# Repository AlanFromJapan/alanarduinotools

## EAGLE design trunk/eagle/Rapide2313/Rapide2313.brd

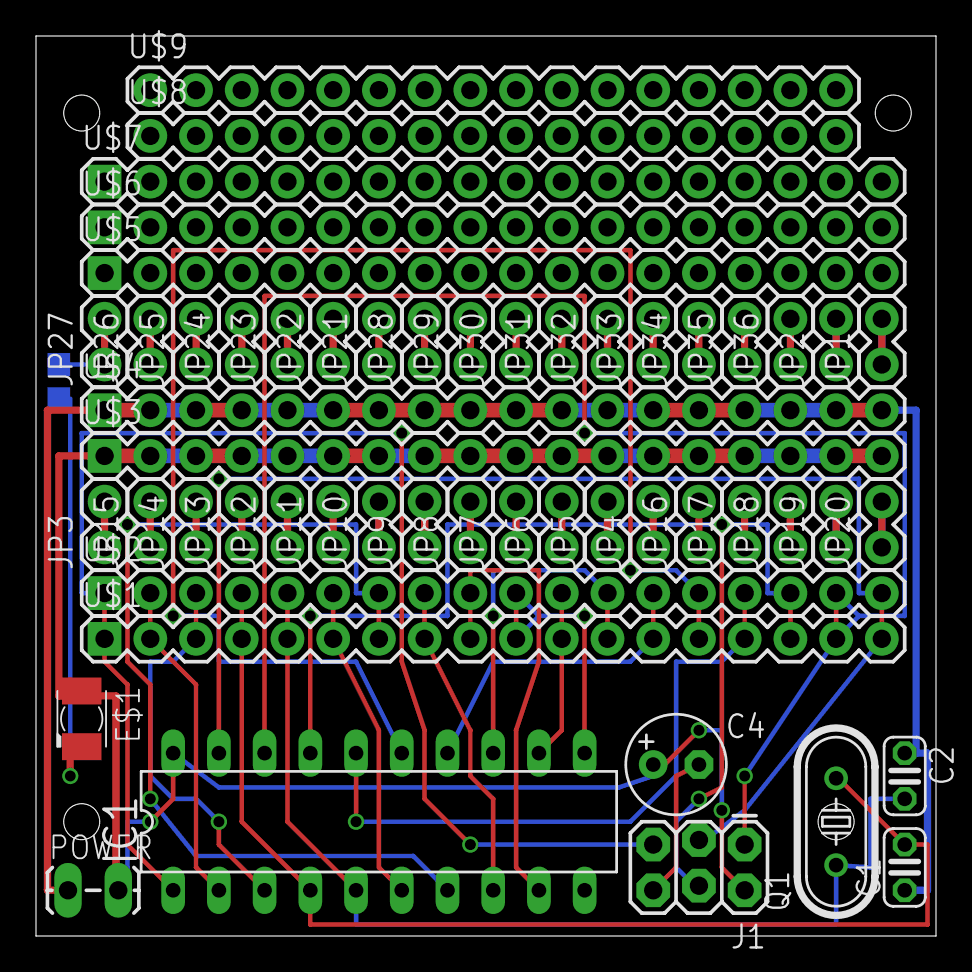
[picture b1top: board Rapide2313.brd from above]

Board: 2 copper layers, 50.0 x 50.0 mm, 53 parts (0 on the bottom side), 56 nets.

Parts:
C1, C2: 22pF; C025-024X044
C4: E2,5-6
E$1: KA-3528ASYC
IC1: AT90S2313P; DIL20
J1: AVR_SPI_PRG_62X3_LOCK; 2X3_LOCK
JP1, JP2, JP3, JP4, JP5, JP6, JP7, JP8, JP9, JP10, JP11, JP12, JP13, JP14, JP15, JP16, JP17, JP18, JP19, JP20, JP21, JP22, JP23, JP24, JP25, JP26, JP27, JP28, JP29, JP30, JP31, JP32, JP33, JP34, JP35, JP36: 1X02
POWER: 1X02_LOCK_LONGPADS
Q1: HC49/S
U$1, U$2, U$3, U$4, U$5, U$6, U$7: M18_; 1X18
U$8, U$9: M18_; 1X16

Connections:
GND: C1.1, C2.1, C4.-, IC1.10, J1.6, U$4.1, U$4.2, U$4.3, U$4.4, U$4.5, U$4.6, U$4.11, U$4.12, U$4.13, U$4.15, U$4.16, U$4.17, U$4.18
MISO: IC1.18, J1.1, U$1.17, U$2.17
MOSI: IC1.17, J1.4, U$1.16, U$2.16
unnamed: C1.2, IC1.4, Q1.2, U$1.4, U$2.4
unnamed: C2.2, IC1.5, Q1.1, U$1.5, U$2.5
unnamed: IC1.2, U$1.2, U$2.2
unnamed: IC1.3, U$1.3, U$2.3
unnamed: IC1.6, U$1.6, U$2.6
unnamed: IC1.7, U$1.7, U$2.7
unnamed: IC1.8, U$1.8, U$2.8
unnamed: IC1.9, U$1.9, U$2.9
unnamed: IC1.11, U$1.10, U$2.10
unnamed: IC1.12, U$1.11, U$2.11
unnamed: IC1.13, U$1.12, U$2.12
unnamed: IC1.14, U$1.13, U$2.13
unnamed: IC1.15, U$1.14, U$2.14
unnamed: IC1.16, U$1.15, U$2.15
RESET: IC1.1, J1.5, U$1.1, U$2.1
S$1: JP27.1, JP27.2
S$2: JP24.1, JP24.2
S$4: JP23.1, JP23.2
S$5: JP22.1, JP22.2
S$6: JP21.1, JP21.2
S$7: JP28.1, JP28.2
S$8: JP29.1, JP29.2
S$9: JP30.1, JP30.2
S$10: JP31.1, JP31.2
S$11: JP32.1, JP32.2
S$12: JP3.1, JP3.2
S$13: JP10.1, JP10.2
S$14: JP9.1, JP9.2
S$15: JP18.1, JP18.2
S$16: JP19.1, JP19.2
S$17: JP20.1, JP20.2
S$18: JP1.1, JP1.2
S$19: JP2.1, JP2.2
S$21: JP26.1, JP26.2
S$22: JP25.1, JP25.2
S$23: JP33.1, JP33.2
S$24: JP34.1, JP34.2
S$25: JP35.1, JP35.2
S$26: JP36.1, JP36.2
S$27: JP17.1, JP17.2
S$28: JP16.1, JP16.2
S$29: JP4.1, JP4.2
S$30: JP5.1, JP5.2
S$31: JP6.1, JP6.2
S$32: JP7.1, JP7.2
S$33: JP8.1, JP8.2
S$34: JP11.1, JP11.2
S$35: JP12.1, JP12.2
S$36: JP13.1, JP13.2
S$37: JP14.1, JP14.2
S$38: JP15.1, JP15.2
SCK: IC1.19, J1.3, U$1.18, U$2.18
VCC: C4.+, IC1.20, J1.2, POWER.2, U$3.1, U$3.2, U$3.3, U$3.4, U$3.5, U$3.6, U$3.7, U$3.8, U$3.12, U$3.13, U$3.15, U$3.16, U$3.17, U$3.18

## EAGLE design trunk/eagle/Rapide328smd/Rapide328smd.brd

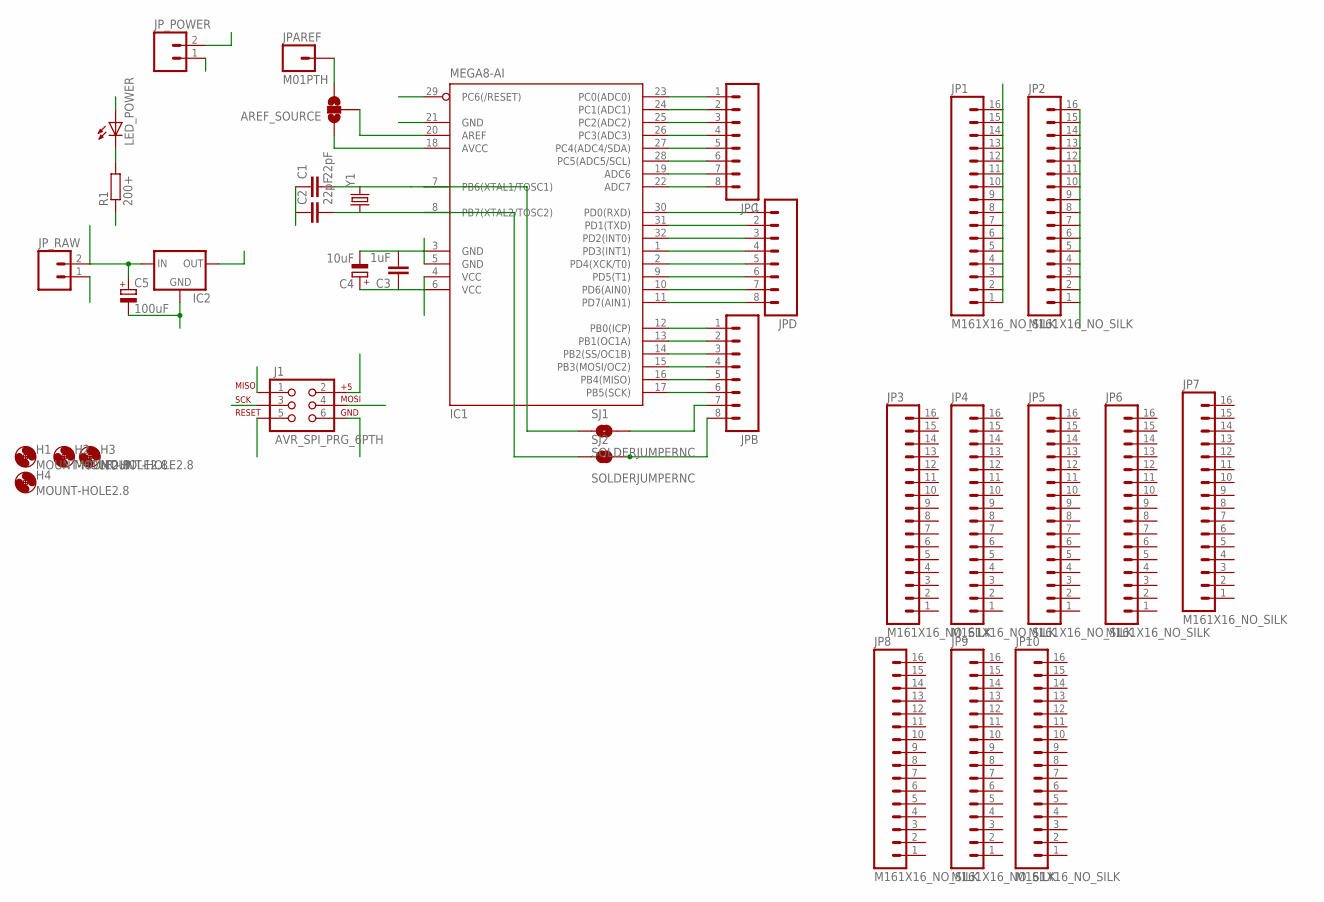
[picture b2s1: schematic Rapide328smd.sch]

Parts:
AREF_SOURCE: SOLDERJUMPER_2WAYPASTE1&2; SJ_3_PASTE1&2
C1, C2: 22pF; C025-024X044
C3: 1uF; C025-024X044
C4: 10uF; E2-5
C5: 100uF; E2-5
H1, H2, H3, H4: MOUNT-HOLE2.8; 2,8
IC1: MEGA8-AI; TQFP32-08
IC2: V_REG_78XXSINK; TO220-IGO
J1: AVR_SPI_PRG_6PTH; 2X3
JP1, JP2, JP3, JP4, JP5, JP6, JP7, JP8, JP9, JP10: M161X16_NO_SILK; 1X16_NO_SILK
JPAREF: M01PTH; 1X01
JPB: M081X08; 1X08
JPC: M081X08; 1X08
JPD: M081X08; 1X08
JP_POWER: M02PTH3; 1X02_LONGPADS
JP_RAW: M02PTH3; 1X02_LONGPADS
LED_POWER: LEDKA-3528ASYC; KA-3528ASYC
R1: 200+; 0204/7
SJ1, SJ2: SOLDERJUMPERNC; SJ_2S
Y1: CRYSTALHC49UV; HC49U-V

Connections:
GND: C1.1, C2.1, C3.2, C4.-, C5.-, IC1.3 (GND), IC1.5 (GND), IC1.21 (GND), IC2.GND, J1.6, JP2.1, JP2.2, JP2.3, JP2.4, JP2.5, JP2.6, JP2.7, JP2.8, JP2.9, JP2.10, JP2.11, JP2.12, JP2.13, JP2.14, JP2.15, JP2.16, JP_POWER.1, JP_RAW.1, R1.1
MISO: IC1.16 (PB4(MISO)), J1.1, JPB.5
MOSI: IC1.15 (PB3(MOSI/OC2)), J1.4, JPB.4
unnamed: C1.2, IC1.7 (PB6(XTAL1/TOSC1)), SJ1.1, Y1.2
unnamed: IC1.25 (PC2(ADC2)), JPC.3
unnamed: IC1.24 (PC1(ADC1)), JPC.2
unnamed: IC1.23 (PC0(ADC0)), JPC.1
unnamed: IC1.22 (ADC7), JPC.8
unnamed: IC1.19 (ADC6), JPC.7
unnamed: IC1.28 (PC5(ADC5/SCL)), JPC.6
unnamed: IC1.27 (PC4(ADC4/SDA)), JPC.5
unnamed: IC1.26 (PC3(ADC3)), JPC.4
unnamed: AREF_SOURCE.2, IC1.20 (AREF)
unnamed: IC1.12 (PB0(ICP)), JPB.1
unnamed: IC1.13 (PB1(OC1A)), JPB.2
unnamed: IC1.14 (PB2(SS/OC1B)), JPB.3
unnamed: JPB.7, SJ1.2
unnamed: JPB.8, SJ2.2
unnamed: C2.2, IC1.8 (PB7(XTAL2/TOSC2)), SJ2.1, Y1.1
unnamed: AREF_SOURCE.3, JPAREF.1
unnamed: IC1.11 (PD7(AIN1)), JPD.8
unnamed: LED_POWER.C, R1.2
unnamed: IC1.10 (PD6(AIN0)), JPD.7
unnamed: IC1.9 (PD5(T1)), JPD.6
unnamed: IC1.2 (PD4(XCK/T0)), JPD.5
unnamed: IC1.1 (PD3(INT1)), JPD.4
unnamed: IC1.32 (PD2(INT0)), JPD.3
unnamed: IC1.31 (PD1(TXD)), JPD.2
unnamed: IC1.30 (PD0(RXD)), JPD.1
RESET: IC1.29 (PC6(/RESET)), J1.5
SCK: IC1.17 (PB5(SCK)), J1.3, JPB.6
VCC: AREF_SOURCE.1, C3.1, C4.+, IC1.4 (VCC), IC1.6 (VCC), IC1.18 (AVCC), IC2.OUT, J1.2, JP1.1, JP1.2, JP1.3, JP1.4, JP1.5, JP1.6, JP1.7, JP1.8, JP1.9, JP1.10, JP1.11, JP1.12, JP1.13, JP1.14, JP1.15, JP1.16, JP_POWER.2, LED_POWER.A
VRAW: C5.+, IC2.IN, JP_RAW.2

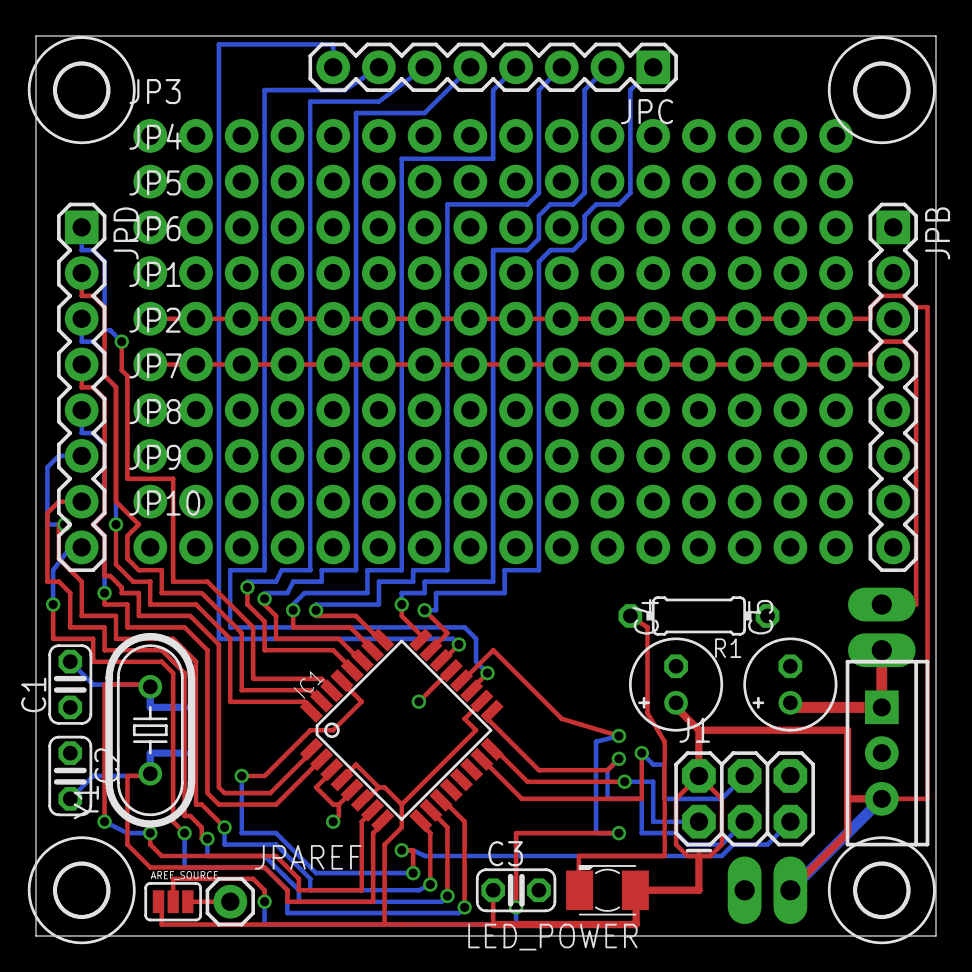
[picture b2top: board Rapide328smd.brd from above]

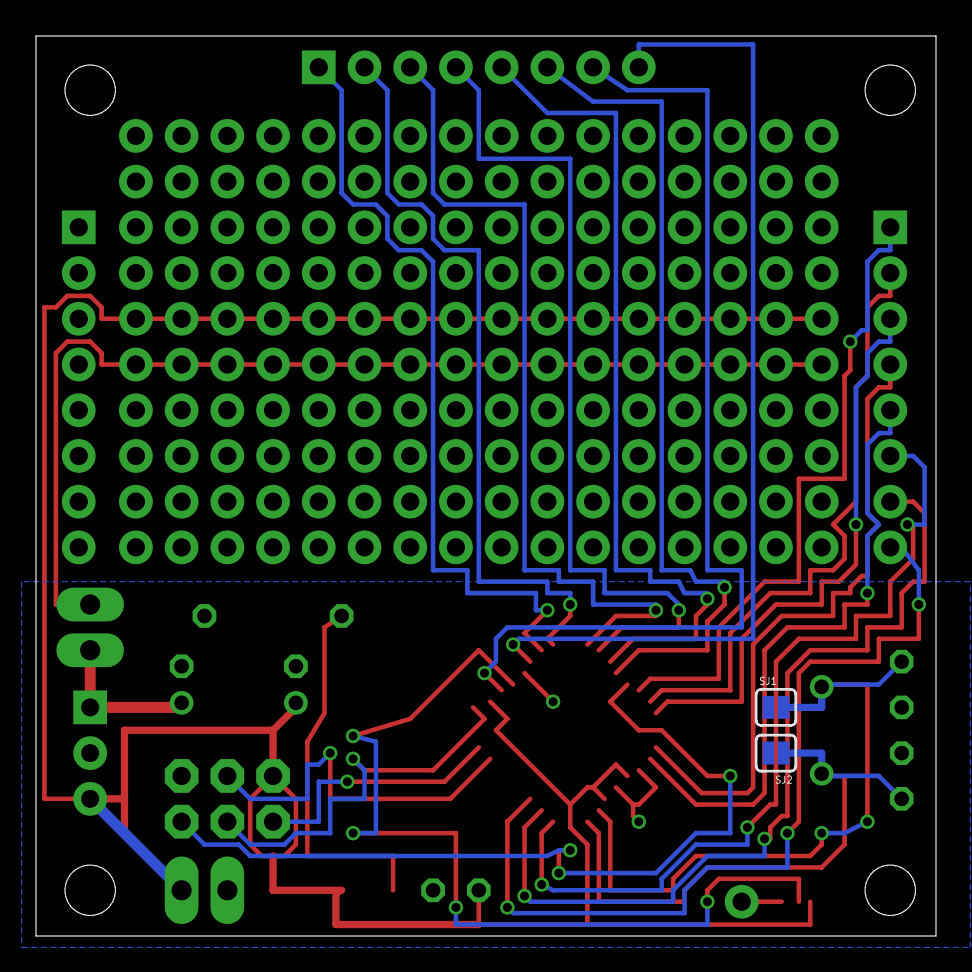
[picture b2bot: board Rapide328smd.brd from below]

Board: 2 copper layers, 50.0 x 50.0 mm, 34 parts (2 on the bottom side), 33 nets.

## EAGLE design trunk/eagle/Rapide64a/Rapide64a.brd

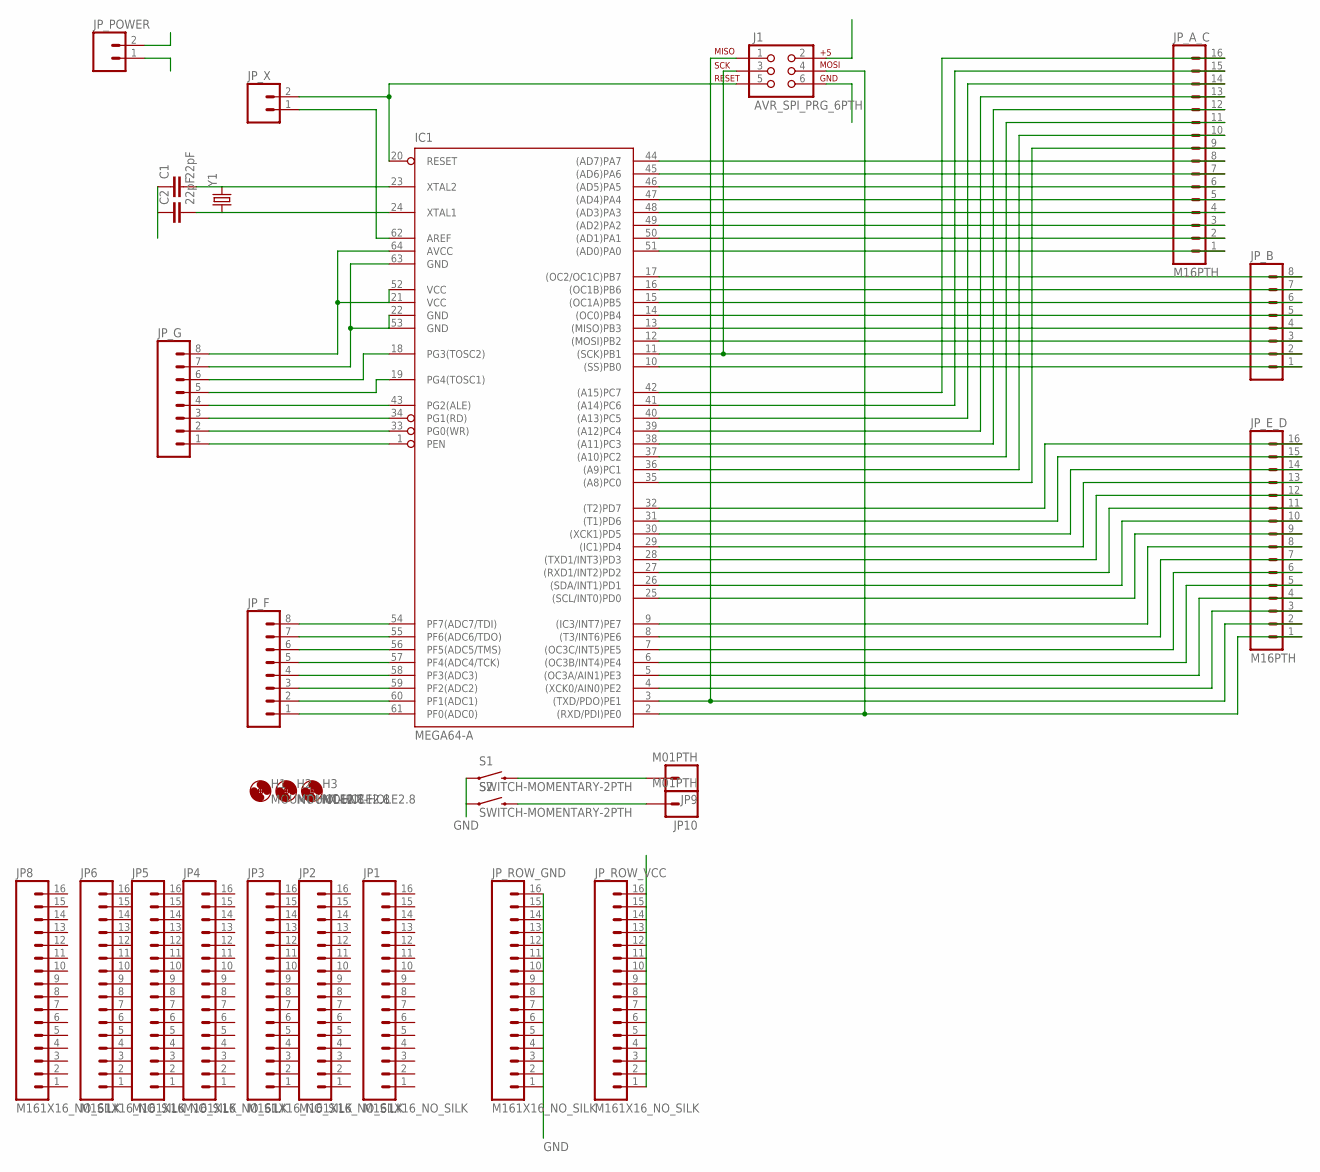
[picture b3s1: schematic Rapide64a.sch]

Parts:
C1, C2: 22pF; C025-024X044
H1, H2, H3: MOUNT-HOLE2.8; 2,8
IC1: MEGA64-A; TQFP64
J1: AVR_SPI_PRG_6PTH; 2X3
JP1, JP2, JP3, JP4, JP5, JP6, JP8: M161X16_NO_SILK; 1X16_NO_SILK
JP9, JP10: M01PTH; 1X01
JP_A_C: M16PTH; 1X16
JP_B: M081X08; 1X08
JP_E_D: M16PTH; 1X16
JP_F: M081X08; 1X08
JP_G: M081X08; 1X08
JP_POWER: M02PTH; 1X02
JP_ROW_GND: M161X16_NO_SILK; 1X16_NO_SILK
JP_ROW_VCC: M161X16_NO_SILK; 1X16_NO_SILK
JP_X: M02PTH; 1X02
S1, S2: SWITCH-MOMENTARY-2PTH; TACTILE-PTH
Y1: CRYSTALHC49UV; HC49U-V

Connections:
GND: C1.1, C2.1, IC1.22 (GND), IC1.53 (GND), IC1.63 (GND), J1.6, JP_G.7, JP_POWER.1, JP_ROW_GND.1, JP_ROW_GND.2, JP_ROW_GND.3, JP_ROW_GND.4, JP_ROW_GND.5, JP_ROW_GND.6, JP_ROW_GND.7, JP_ROW_GND.8, JP_ROW_GND.9, JP_ROW_GND.10, JP_ROW_GND.11, JP_ROW_GND.12, JP_ROW_GND.13, JP_ROW_GND.14, JP_ROW_GND.15, JP_ROW_GND.16, S1.1, S2.1
MISO: IC1.3 ((TXD/PDO)PE1), J1.1, JP_E_D.2
MOSI: IC1.2 ((RXD/PDI)PE0), J1.4, JP_E_D.1
unnamed: IC1.6 ((OC3B/INT4)PE4), JP_E_D.5
unnamed: IC1.7 ((OC3C/INT5)PE5), JP_E_D.6
unnamed: IC1.8 ((T3/INT6)PE6), JP_E_D.7
unnamed: IC1.25 ((SCL/INT0)PD0), JP_E_D.9
unnamed: IC1.9 ((IC3/INT7)PE7), JP_E_D.8
unnamed: IC1.26 ((SDA/INT1)PD1), JP_E_D.10
unnamed: IC1.27 ((RXD1/INT2)PD2), JP_E_D.11
unnamed: IC1.58 (PF3(ADC3)), JP_F.4
unnamed: IC1.57 (PF4(ADC4/TCK)), JP_F.5
unnamed: IC1.56 (PF5(ADC5/TMS)), JP_F.6
unnamed: IC1.55 (PF6(ADC6/TDO)), JP_F.7
unnamed: IC1.54 (PF7(ADC7/TDI)), JP_F.8
unnamed: IC1.48 ((AD3)PA3), JP_A_C.4
unnamed: IC1.10 ((SS)PB0), JP_B.1
unnamed: IC1.49 ((AD2)PA2), JP_A_C.3
unnamed: IC1.17 ((OC2/OC1C)PB7), JP_B.8
unnamed: IC1.1 (PEN), JP_G.1
unnamed: IC1.33 (PG0(WR)), JP_G.2
unnamed: IC1.34 (PG1(RD)), JP_G.3
unnamed: IC1.18 (PG3(TOSC2)), JP_G.6
unnamed: IC1.19 (PG4(TOSC1)), JP_G.5
unnamed: IC1.39 ((A12)PC4), JP_A_C.13
unnamed: IC1.12 ((MOSI)PB2), JP_B.3
unnamed: IC1.13 ((MISO)PB3), JP_B.4
unnamed: IC1.43 (PG2(ALE)), JP_G.4
unnamed: IC1.47 ((AD4)PA4), JP_A_C.5
unnamed: IC1.46 ((AD5)PA5), JP_A_C.6
unnamed: IC1.45 ((AD6)PA6), JP_A_C.7
unnamed: JP9.1, S1.3 (2)
unnamed: IC1.14 ((OC0)PB4), JP_B.5
unnamed: IC1.51 ((AD0)PA0), JP_A_C.1
unnamed: IC1.50 ((AD1)PA1), JP_A_C.2
unnamed: IC1.15 ((OC1A)PB5), JP_B.6
unnamed: JP10.1, S2.3 (2)
unnamed: IC1.44 ((AD7)PA7), JP_A_C.8
unnamed: IC1.16 ((OC1B)PB6), JP_B.7
unnamed: IC1.42 ((A15)PC7), JP_A_C.16
unnamed: IC1.41 ((A14)PC6), JP_A_C.15
unnamed: IC1.40 ((A13)PC5), JP_A_C.14
unnamed: IC1.35 ((A8)PC0), JP_A_C.9
unnamed: IC1.62 (AREF), JP_X.1
unnamed: C1.2, IC1.23 (XTAL2), Y1.2
unnamed: C2.2, IC1.24 (XTAL1), Y1.1
unnamed: IC1.4 ((XCK0/AIN0)PE2), JP_E_D.3
unnamed: IC1.5 ((OC3A/AIN1)PE3), JP_E_D.4
unnamed: IC1.28 ((TXD1/INT3)PD3), JP_E_D.12
unnamed: IC1.29 ((IC1)PD4), JP_E_D.13
unnamed: IC1.30 ((XCK1)PD5), JP_E_D.14
unnamed: IC1.31 ((T1)PD6), JP_E_D.15
unnamed: IC1.32 ((T2)PD7), JP_E_D.16
unnamed: IC1.38 ((A11)PC3), JP_A_C.12
unnamed: IC1.61 (PF0(ADC0)), JP_F.1
unnamed: IC1.60 (PF1(ADC1)), JP_F.2
unnamed: IC1.59 (PF2(ADC2)), JP_F.3
unnamed: IC1.37 ((A10)PC2), JP_A_C.11
unnamed: IC1.36 ((A9)PC1), JP_A_C.10
RESET: IC1.20 (RESET), J1.5, JP_X.2
SCK: IC1.11 ((SCK)PB1), J1.3, JP_B.2
VCC: IC1.21 (VCC), IC1.52 (VCC), IC1.64 (AVCC), J1.2, JP_G.8, JP_POWER.2, JP_ROW_VCC.1, JP_ROW_VCC.2, JP_ROW_VCC.3, JP_ROW_VCC.4, JP_ROW_VCC.5, JP_ROW_VCC.6, JP_ROW_VCC.7, JP_ROW_VCC.8, JP_ROW_VCC.9, JP_ROW_VCC.10, JP_ROW_VCC.11, JP_ROW_VCC.12, JP_ROW_VCC.13, JP_ROW_VCC.14, JP_ROW_VCC.15, JP_ROW_VCC.16

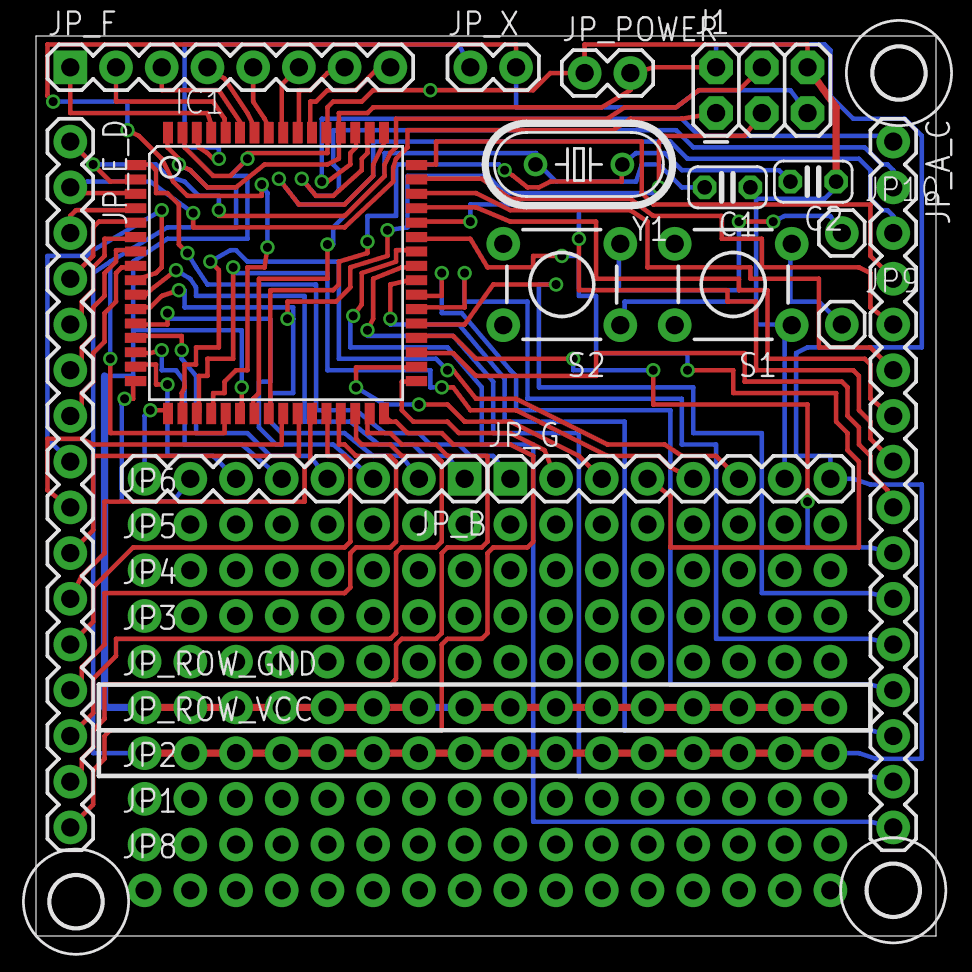
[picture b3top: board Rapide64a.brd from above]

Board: 2 copper layers, 50.0 x 50.0 mm, 28 parts (0 on the bottom side), 62 nets.

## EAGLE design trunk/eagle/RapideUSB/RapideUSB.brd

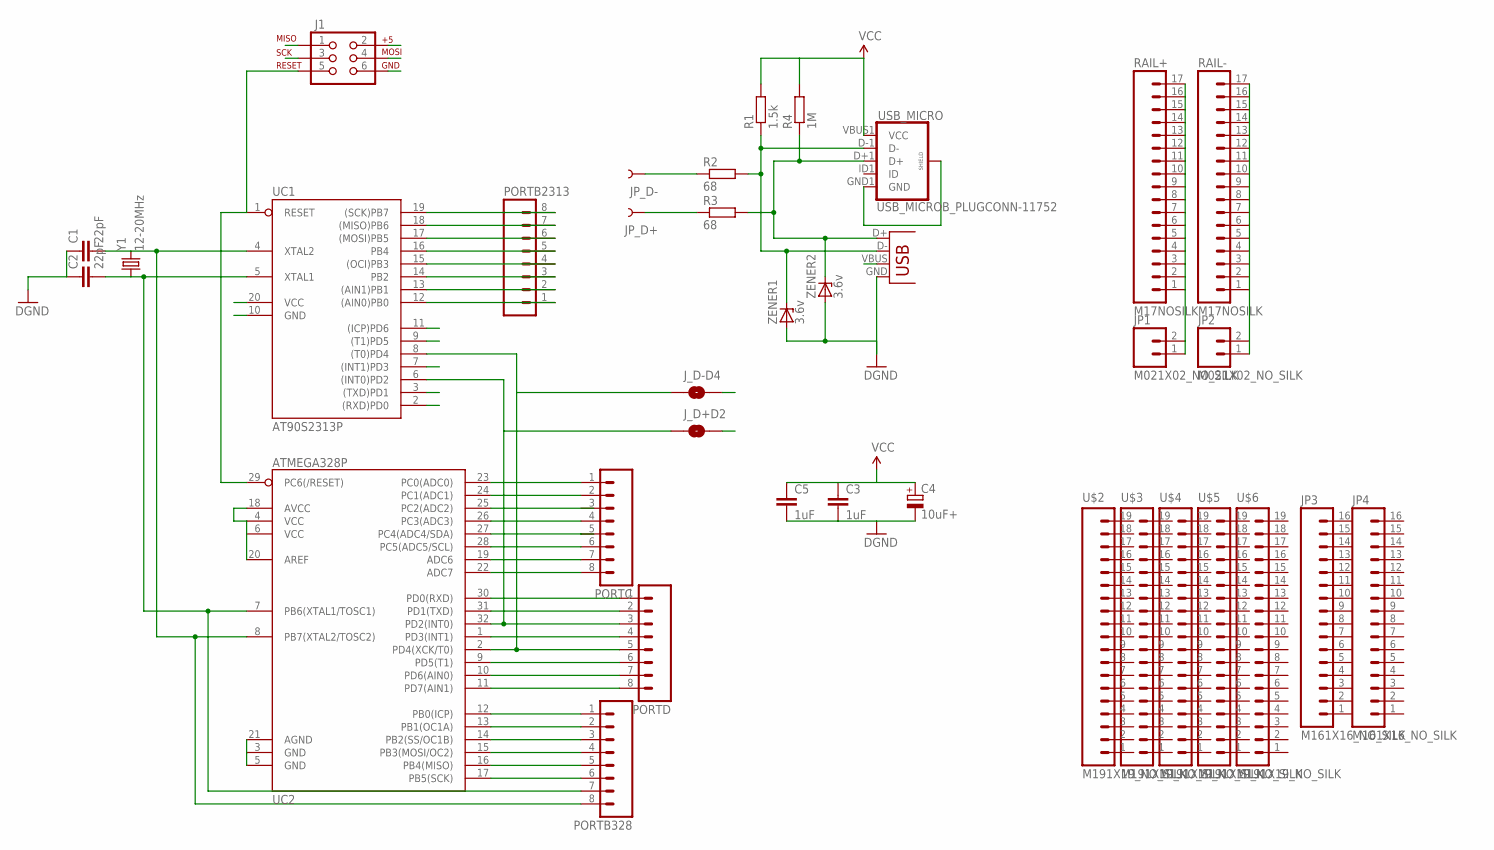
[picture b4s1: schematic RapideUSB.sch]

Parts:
C1, C2: 22pF; C025-024X044
C3, C5: 1uF; C025-024X044
C4: 10uF+; E2-5
J1: AVR_SPI_PRG_6PTH; 2X3
JP1, JP2: M021X02_NO_SILK; 1X02_NO_SILK
JP3, JP4: M161X16_NO_SILK; 1X16_NO_SILK
JP_D+: TEST-POINT3X5; PAD.03X.05
JP_D-: TEST-POINT3X5; PAD.03X.05
J_D+D2: JUMPER-PAD-2-NOYES_SILK; PAD-JUMPER-2-NO_YES_SILK
J_D-D4: JUMPER-PAD-2-NOYES_SILK; PAD-JUMPER-2-NO_YES_SILK
PORTB328, PORTB2313: M081X08; 1X08
PORTC: M081X08; 1X08
PORTD: M081X08; 1X08
R1: 1.5k; 0204V
R2, R3: 68; 0204V
R4: 1M; 0204V
RAIL+: M17NOSILK; 1X17_NO_SILK
RAIL-: M17NOSILK; 1X17_NO_SILK
U$2, U$3, U$4, U$5, U$6: M191X19_NO_SILK; 1X19_NO_SILK
UC1: AT90S2313P; DIL20
UC2: ATMEGA328P; TQFP32-08
USB_MICRO: USB_MICROB_PLUGCONN-11752; USB-B-MICRO-SMD_V03
USB_MINI: USBSMD; USB-MINIB
Y1: 12-20MHz; HC49U-V
ZENER1, ZENER2: 3.6v; ZDIO-2.5

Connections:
B0: PORTB328.1, UC2.12 (PB0(ICP))
B1: PORTB328.2, UC2.13 (PB1(OC1A))
B2: PORTB328.3, UC2.14 (PB2(SS/OC1B))
B6: C2.2, PORTB328.7, UC1.5 (XTAL1), UC2.7 (PB6(XTAL1/TOSC1)), Y1.1
B7: C1.2, PORTB328.8, UC1.4 (XTAL2), UC2.8 (PB7(XTAL2/TOSC2)), Y1.2
D0: PORTD.1, UC1.2 ((RXD)PD0), UC2.30 (PD0(RXD))
D1: PORTD.2, UC1.3 ((TXD)PD1), UC2.31 (PD1(TXD))
D2: J_D+D2.1, PORTD.3, UC1.6 ((INT0)PD2), UC2.32 (PD2(INT0))
D3: PORTD.4, UC1.7 ((INT1)PD3), UC2.1 (PD3(INT1))
D4: J_D-D4.1, PORTD.5, UC1.8 ((T0)PD4), UC2.2 (PD4(XCK/T0))
D5: UC1.9 ((T1)PD5)
D6: PORTD.7, UC1.11 ((ICP)PD6), UC2.10 (PD6(AIN0))
D7: PORTD.8, UC2.11 (PD7(AIN1))
D+: JP_D+.P$1, J_D+D2.2, R3.1
D-: JP_D-.P$1, J_D-D4.2, R2.1
GND: C1.1, C2.1, C3.2, C4.-, C5.2, J1.6, JP2.1, JP2.2, RAIL-.1, RAIL-.2, RAIL-.3, RAIL-.4, RAIL-.5, RAIL-.6, RAIL-.7, RAIL-.8, RAIL-.9, RAIL-.10, RAIL-.11, RAIL-.12, RAIL-.13, RAIL-.14, RAIL-.15, RAIL-.16, RAIL-.17, UC1.10 (GND), UC2.3 (GND), UC2.5 (GND), UC2.21 (AGND), USB_MICRO.GND1 (GND), USB_MICRO.SHIELD1 (SHIELD), USB_MICRO.SHIELD2 (SHIELD), USB_MICRO.SHIELD3 (SHIELD), USB_MINI.GND, ZENER1.A, ZENER2.A
MISO: J1.1, PORTB328.5, PORTB2313.7, UC1.18 ((MISO)PB6), UC2.16 (PB4(MISO))
MOSI: J1.4, PORTB328.4, PORTB2313.6, UC1.17 ((MOSI)PB5), UC2.15 (PB3(MOSI/OC2))
unnamed: PORTB2313.5, UC1.16 (PB4)
unnamed: PORTB2313.4, UC1.15 ((OCI)PB3)
unnamed: PORTB2313.3, UC1.14 (PB2)
unnamed: PORTB2313.2, UC1.13 ((AIN1)PB1)
unnamed: PORTC.1, UC2.23 (PC0(ADC0))
unnamed: PORTC.2, UC2.24 (PC1(ADC1))
unnamed: PORTC.4, UC2.26 (PC3(ADC3))
unnamed: PORTC.5, UC2.27 (PC4(ADC4/SDA))
unnamed: PORTC.6, UC2.28 (PC5(ADC5/SCL))
unnamed: PORTC.7, UC2.19 (ADC6)
unnamed: PORTC.8, UC2.22 (ADC7)
unnamed: PORTB2313.1, UC1.12 ((AIN0)PB0)
unnamed: PORTD.6, UC2.9 (PD5(T1))
RESET: J1.5, UC1.1 (RESET), UC2.29 (PC6(/RESET))
SCK: J1.3, PORTB328.6, PORTB2313.8, UC1.19 ((SCK)PB7), UC2.17 (PB5(SCK))
USBD+: R3.2, R4.1, USB_MICRO.D+1 (D+), USB_MINI.D+, ZENER2.C
USBD-: R1.1, R2.2, USB_MICRO.D-1 (D-), USB_MINI.D-, ZENER1.C
VCC: C3.1, C4.+, C5.1, J1.2, JP1.1, JP1.2, R1.2, R4.2, RAIL+.1, RAIL+.2, RAIL+.3, RAIL+.4, RAIL+.5, RAIL+.6, RAIL+.7, RAIL+.8, RAIL+.9, RAIL+.10, RAIL+.11, RAIL+.12, RAIL+.13, RAIL+.14, RAIL+.15, RAIL+.16, RAIL+.17, UC1.20 (VCC), UC2.4 (VCC), UC2.6 (VCC), UC2.18 (AVCC), UC2.20 (AREF), USB_MICRO.VBUS1 (VCC), USB_MINI.VBUS

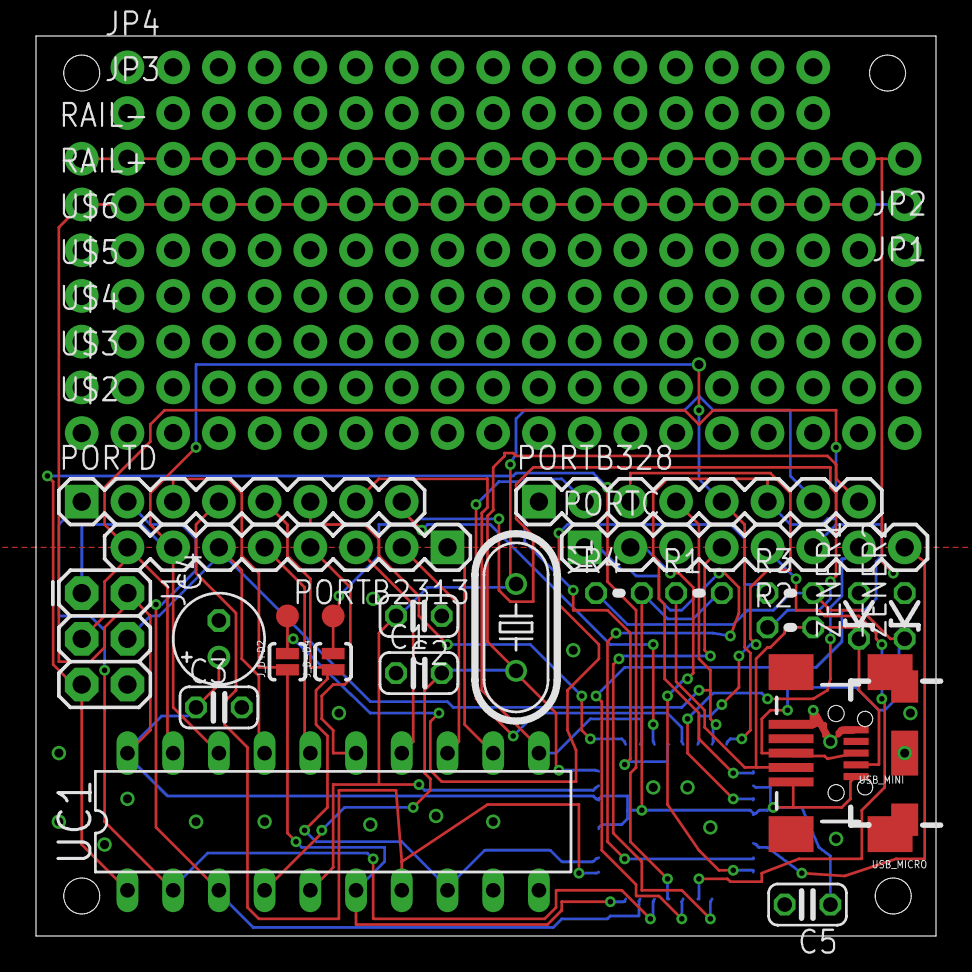
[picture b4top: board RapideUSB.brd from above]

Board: 4 copper layers, 50.0 x 50.0 mm, 37 parts (1 on the bottom side), 35 nets.

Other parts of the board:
U$1: VUSB_LOGO

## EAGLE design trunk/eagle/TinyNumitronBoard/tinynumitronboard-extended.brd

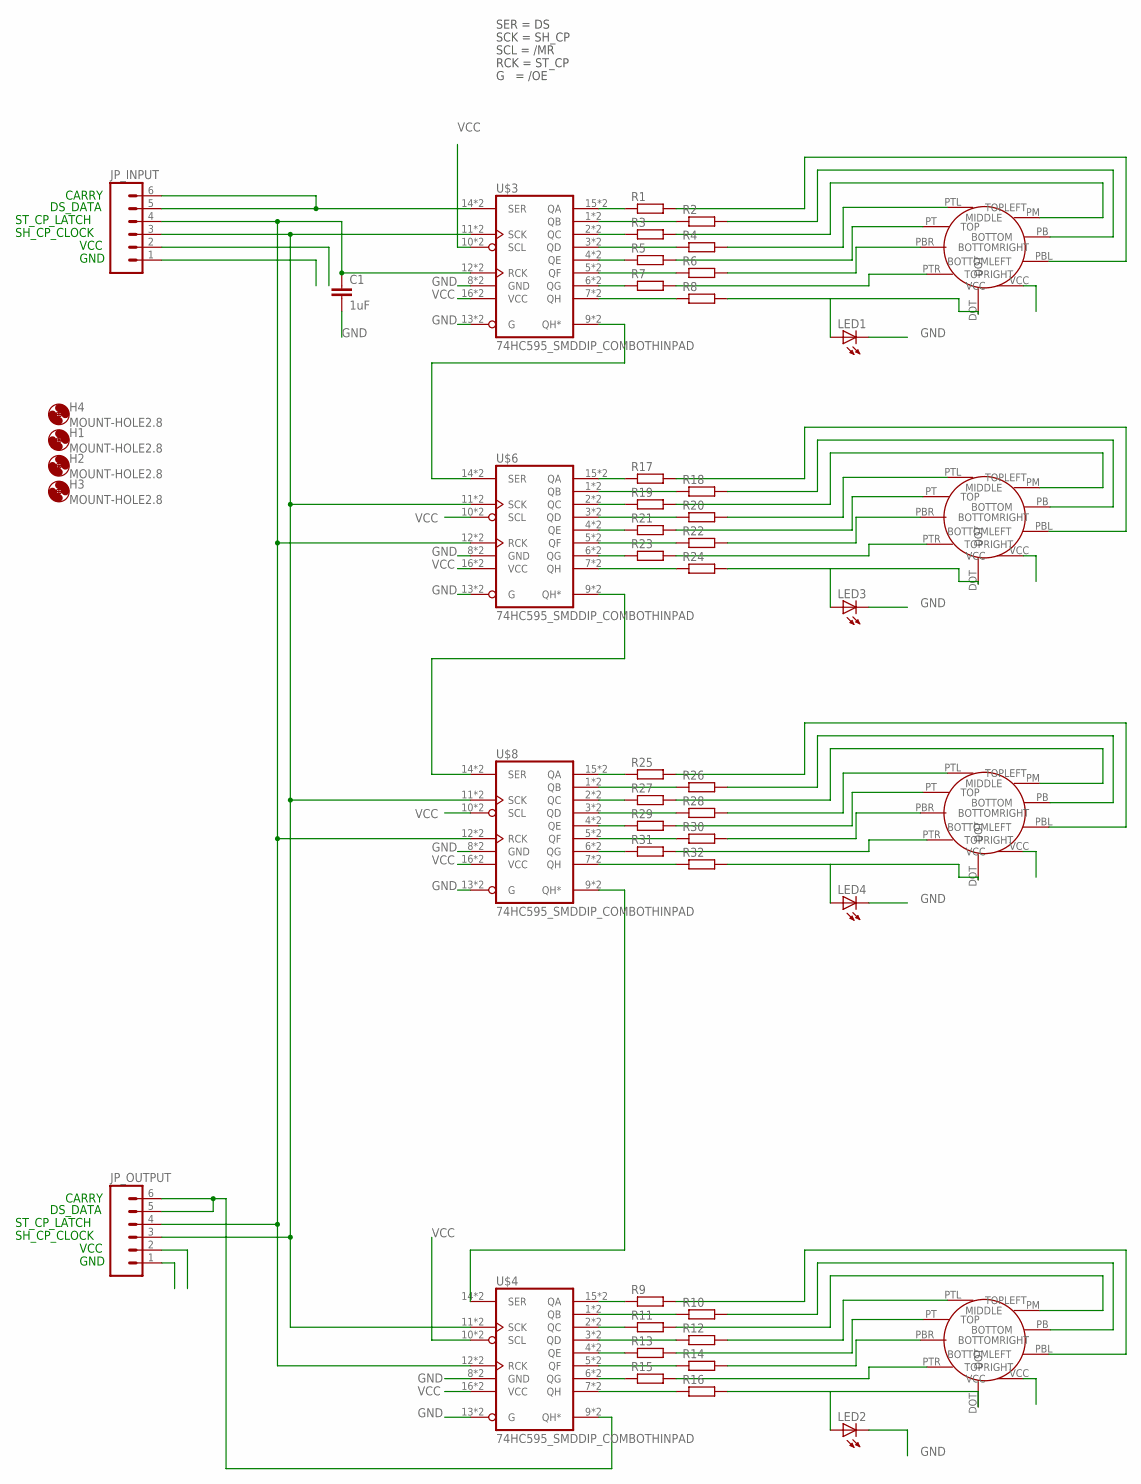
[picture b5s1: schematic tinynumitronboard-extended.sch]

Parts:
C1: 1uF; C050-024X044
H1, H2, H3, H4: MOUNT-HOLE2.8; 2,8
JP_INPUT: M06SIP; 1X06
JP_OUTPUT: M06SIP; 1X06
LED1, LED2, LED3, LED4: LEDKA-3528ASYC; KA-3528ASYC
R1, R2, R3, R4, R5, R6, R7, R8, R9, R10, R11, R12, R13, R14, R15, R16, R17, R18, R19, R20, R21, R22, R23, R24, R25, R26, R27, R28, R29, R30, R31, R32: R-EU_0207/10; 0207/10
U$1, U$2, U$5, U$7: IV16TINY_NUMITRON; IV16TINY_NUMITRON_PAC
U$3, U$4, U$6, U$8: 74HC595_SMDDIP_COMBOTHINPAD; DIL16_SO16_PAC2

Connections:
GND: C1.2, JP_INPUT.1, JP_OUTPUT.1, LED1.C, LED2.C, LED3.C, LED4.C, U$4.8 (GND), U$4.13 (G); also elsewhere on the board
unnamed: R1.2, U$1.PBL (BOTTOMLEFT)
unnamed: R2.2, U$1.PB (BOTTOM)
unnamed: R3.2, U$1.PM (MIDDLE)
unnamed: R4.2, U$1.PTL (TOPLEFT)
unnamed: R5.2, U$1.PT (TOP)
unnamed: R6.2, U$1.PBR (BOTTOMRIGHT)
unnamed: R7.2, U$1.PTR (TOPRIGHT)
unnamed 8: R1.1, U$3.15 (QA); also elsewhere on the board
unnamed 9: R2.1, U$3.1 (QB); also elsewhere on the board
unnamed 10: R3.1, U$3.2 (QC); also elsewhere on the board
unnamed 11: R4.1, U$3.3 (QD); also elsewhere on the board
unnamed 12: R5.1, U$3.4 (QE); also elsewhere on the board
unnamed 13: R6.1, U$3.5 (QF); also elsewhere on the board
unnamed 14: R7.1, U$3.6 (QG); also elsewhere on the board
unnamed 15: R8.1, U$3.7 (QH); also elsewhere on the board
unnamed: LED1.A, R8.2, U$1.DOT
unnamed: R9.2, U$2.PBL (BOTTOMLEFT)
unnamed: R10.2, U$2.PB (BOTTOM)
unnamed 19: JP_OUTPUT.5, JP_OUTPUT.6, U$4.9 (QH*); also elsewhere on the board
unnamed: R11.2, U$2.PM (MIDDLE)
unnamed: R12.2, U$2.PTL (TOPLEFT)
unnamed: R13.2, U$2.PT (TOP)
unnamed: R14.2, U$2.PBR (BOTTOMRIGHT)
unnamed: R15.2, U$2.PTR (TOPRIGHT)
unnamed 26: R9.1, U$4.15 (QA); also elsewhere on the board
unnamed 27: R10.1, U$4.1 (QB); also elsewhere on the board
unnamed 28: R11.1, U$4.2 (QC); also elsewhere on the board
unnamed 29: R12.1, U$4.3 (QD); also elsewhere on the board
unnamed 30: R13.1, U$4.4 (QE); also elsewhere on the board
unnamed 31: R14.1, U$4.5 (QF); also elsewhere on the board
unnamed 32: R15.1, U$4.6 (QG); also elsewhere on the board
unnamed 33: R16.1, U$4.7 (QH); also elsewhere on the board
unnamed: R17.2, U$5.PBL (BOTTOMLEFT)
unnamed: R18.2, U$5.PB (BOTTOM)
unnamed: R19.2, U$5.PM (MIDDLE)
unnamed: R20.2, U$5.PTL (TOPLEFT)
unnamed: R21.2, U$5.PT (TOP)
unnamed: R22.2, U$5.PBR (BOTTOMRIGHT)
unnamed: R23.2, U$5.PTR (TOPRIGHT)
unnamed 41: R17.1, U$6.15 (QA); also elsewhere on the board
unnamed 42: R18.1, U$6.1 (QB); also elsewhere on the board
unnamed 43: R19.1, U$6.2 (QC); also elsewhere on the board
unnamed 44: R20.1, U$6.3 (QD); also elsewhere on the board
unnamed 45: R21.1, U$6.4 (QE); also elsewhere on the board
unnamed 46: R22.1, U$6.5 (QF); also elsewhere on the board
unnamed 47: R23.1, U$6.6 (QG); also elsewhere on the board
unnamed 48: R24.1, U$6.7 (QH); also elsewhere on the board
unnamed: R25.2, U$7.PBL (BOTTOMLEFT)
unnamed: R26.2, U$7.PB (BOTTOM)
unnamed: R27.2, U$7.PM (MIDDLE)
unnamed: R28.2, U$7.PTL (TOPLEFT)
unnamed: R29.2, U$7.PT (TOP)
unnamed: R30.2, U$7.PBR (BOTTOMRIGHT)
unnamed: R31.2, U$7.PTR (TOPRIGHT)
unnamed 57: R25.1, U$8.15 (QA); also elsewhere on the board
unnamed 58: R26.1, U$8.1 (QB); also elsewhere on the board
unnamed 59: R27.1, U$8.2 (QC); also elsewhere on the board
unnamed 60: R28.1, U$8.3 (QD); also elsewhere on the board
unnamed 61: R29.1, U$8.4 (QE); also elsewhere on the board
unnamed 62: R30.1, U$8.5 (QF); also elsewhere on the board
unnamed 63: R31.1, U$8.6 (QG); also elsewhere on the board
unnamed 64: R32.1, U$8.7 (QH); also elsewhere on the board
RCK: C1.1, JP_INPUT.4, JP_OUTPUT.4, U$4.12 (RCK); also elsewhere on the board
SCK: JP_INPUT.3, JP_OUTPUT.3, U$4.11 (SCK); also elsewhere on the board
SER: JP_INPUT.5, JP_INPUT.6; also elsewhere on the board
VCC: JP_INPUT.2, JP_OUTPUT.2, U$1.VCC, U$2.VCC, U$4.10 (SCL), U$4.16 (VCC), U$5.VCC, U$7.VCC; also elsewhere on the board

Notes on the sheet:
SER = DS
SCK = SH_CP
SCL = /MR
RCK = ST_CP
G = /OE
GND
VCC
SH_CP_CLOCK
ST_CP_LATCH
DS_DATA
CARRY

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
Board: 2 copper layers, 51 parts (4 on the bottom side), 73 nets, no tracks yet.

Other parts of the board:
UC1, UC2, UC3, UC4: 74HC595_SMDDIP_COMBOTHINPAD; DIL16_SO16_PAC2

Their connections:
GND: UC1.8, UC1.13, UC1.S8, UC1.S13, UC2.8, UC2.13, UC2.S8, UC2.S13, UC3.8, UC3.13, UC3.S8, UC3.S13, UC4.8, UC4.13, UC4.S8, UC4.S13; also elsewhere on the board
unnamed 8: UC1.15, UC1.S15; also elsewhere on the board
unnamed 9: UC1.1, UC1.S1; also elsewhere on the board
unnamed 10: UC1.2, UC1.S2; also elsewhere on the board
unnamed 11: UC1.3, UC1.S3; also elsewhere on the board
unnamed 12: UC1.4, UC1.S4; also elsewhere on the board
unnamed 13: UC1.5, UC1.S5; also elsewhere on the board
unnamed 14: UC1.6, UC1.S6; also elsewhere on the board
unnamed 15: UC1.7, UC1.S7; also elsewhere on the board
unnamed 19: UC4.9, UC4.S9; also elsewhere on the board
unnamed: UC1.9, UC1.S9, UC2.14, UC2.S14
unnamed 26: UC4.15, UC4.S15; also elsewhere on the board
unnamed 27: UC4.1, UC4.S1; also elsewhere on the board
unnamed 28: UC4.2, UC4.S2; also elsewhere on the board
unnamed 29: UC4.3, UC4.S3; also elsewhere on the board
unnamed 30: UC4.4, UC4.S4; also elsewhere on the board
unnamed 31: UC4.5, UC4.S5; also elsewhere on the board
unnamed 32: UC4.6, UC4.S6; also elsewhere on the board
unnamed 33: UC4.7, UC4.S7; also elsewhere on the board
unnamed 41: UC2.15, UC2.S15; also elsewhere on the board
unnamed 42: UC2.1, UC2.S1; also elsewhere on the board
unnamed 43: UC2.2, UC2.S2; also elsewhere on the board
unnamed 44: UC2.3, UC2.S3; also elsewhere on the board
unnamed 45: UC2.4, UC2.S4; also elsewhere on the board
unnamed 46: UC2.5, UC2.S5; also elsewhere on the board
unnamed 47: UC2.6, UC2.S6; also elsewhere on the board
unnamed 48: UC2.7, UC2.S7; also elsewhere on the board
unnamed: UC2.9, UC2.S9, UC3.14, UC3.S14
unnamed 57: UC3.15, UC3.S15; also elsewhere on the board
unnamed 58: UC3.1, UC3.S1; also elsewhere on the board
unnamed 59: UC3.2, UC3.S2; also elsewhere on the board
unnamed 60: UC3.3, UC3.S3; also elsewhere on the board
unnamed 61: UC3.4, UC3.S4; also elsewhere on the board
unnamed 62: UC3.5, UC3.S5; also elsewhere on the board
unnamed 63: UC3.6, UC3.S6; also elsewhere on the board
unnamed 64: UC3.7, UC3.S7; also elsewhere on the board
unnamed: UC3.9, UC3.S9, UC4.14, UC4.S14
RCK: UC1.12, UC1.S12, UC2.12, UC2.S12, UC3.12, UC3.S12, UC4.12, UC4.S12; also elsewhere on the board
SCK: UC1.11, UC1.S11, UC2.11, UC2.S11, UC3.11, UC3.S11, UC4.11, UC4.S11; also elsewhere on the board
SER: UC1.14, UC1.S14; also elsewhere on the board
VCC: UC1.10, UC1.16, UC1.S10, UC1.S16, UC2.10, UC2.16, UC2.S10, UC2.S16, UC3.10, UC3.16, UC3.S10, UC3.S16, UC4.10, UC4.16, UC4.S10, UC4.S16; also elsewhere on the board

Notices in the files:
parts and their libraries:
SparkFun: Licensing: CC v3.0 Share-Alike You are welcome to use this library for commercial purposes.
SparkFun-DigitalIC: Licensing: Creative Commons ShareAlike 4.0 International - https://creativecommons.org/licenses/by-sa/4.0
